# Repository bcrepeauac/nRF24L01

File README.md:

# nRF24L01
nRF24L01 adapter board for the SumoShield

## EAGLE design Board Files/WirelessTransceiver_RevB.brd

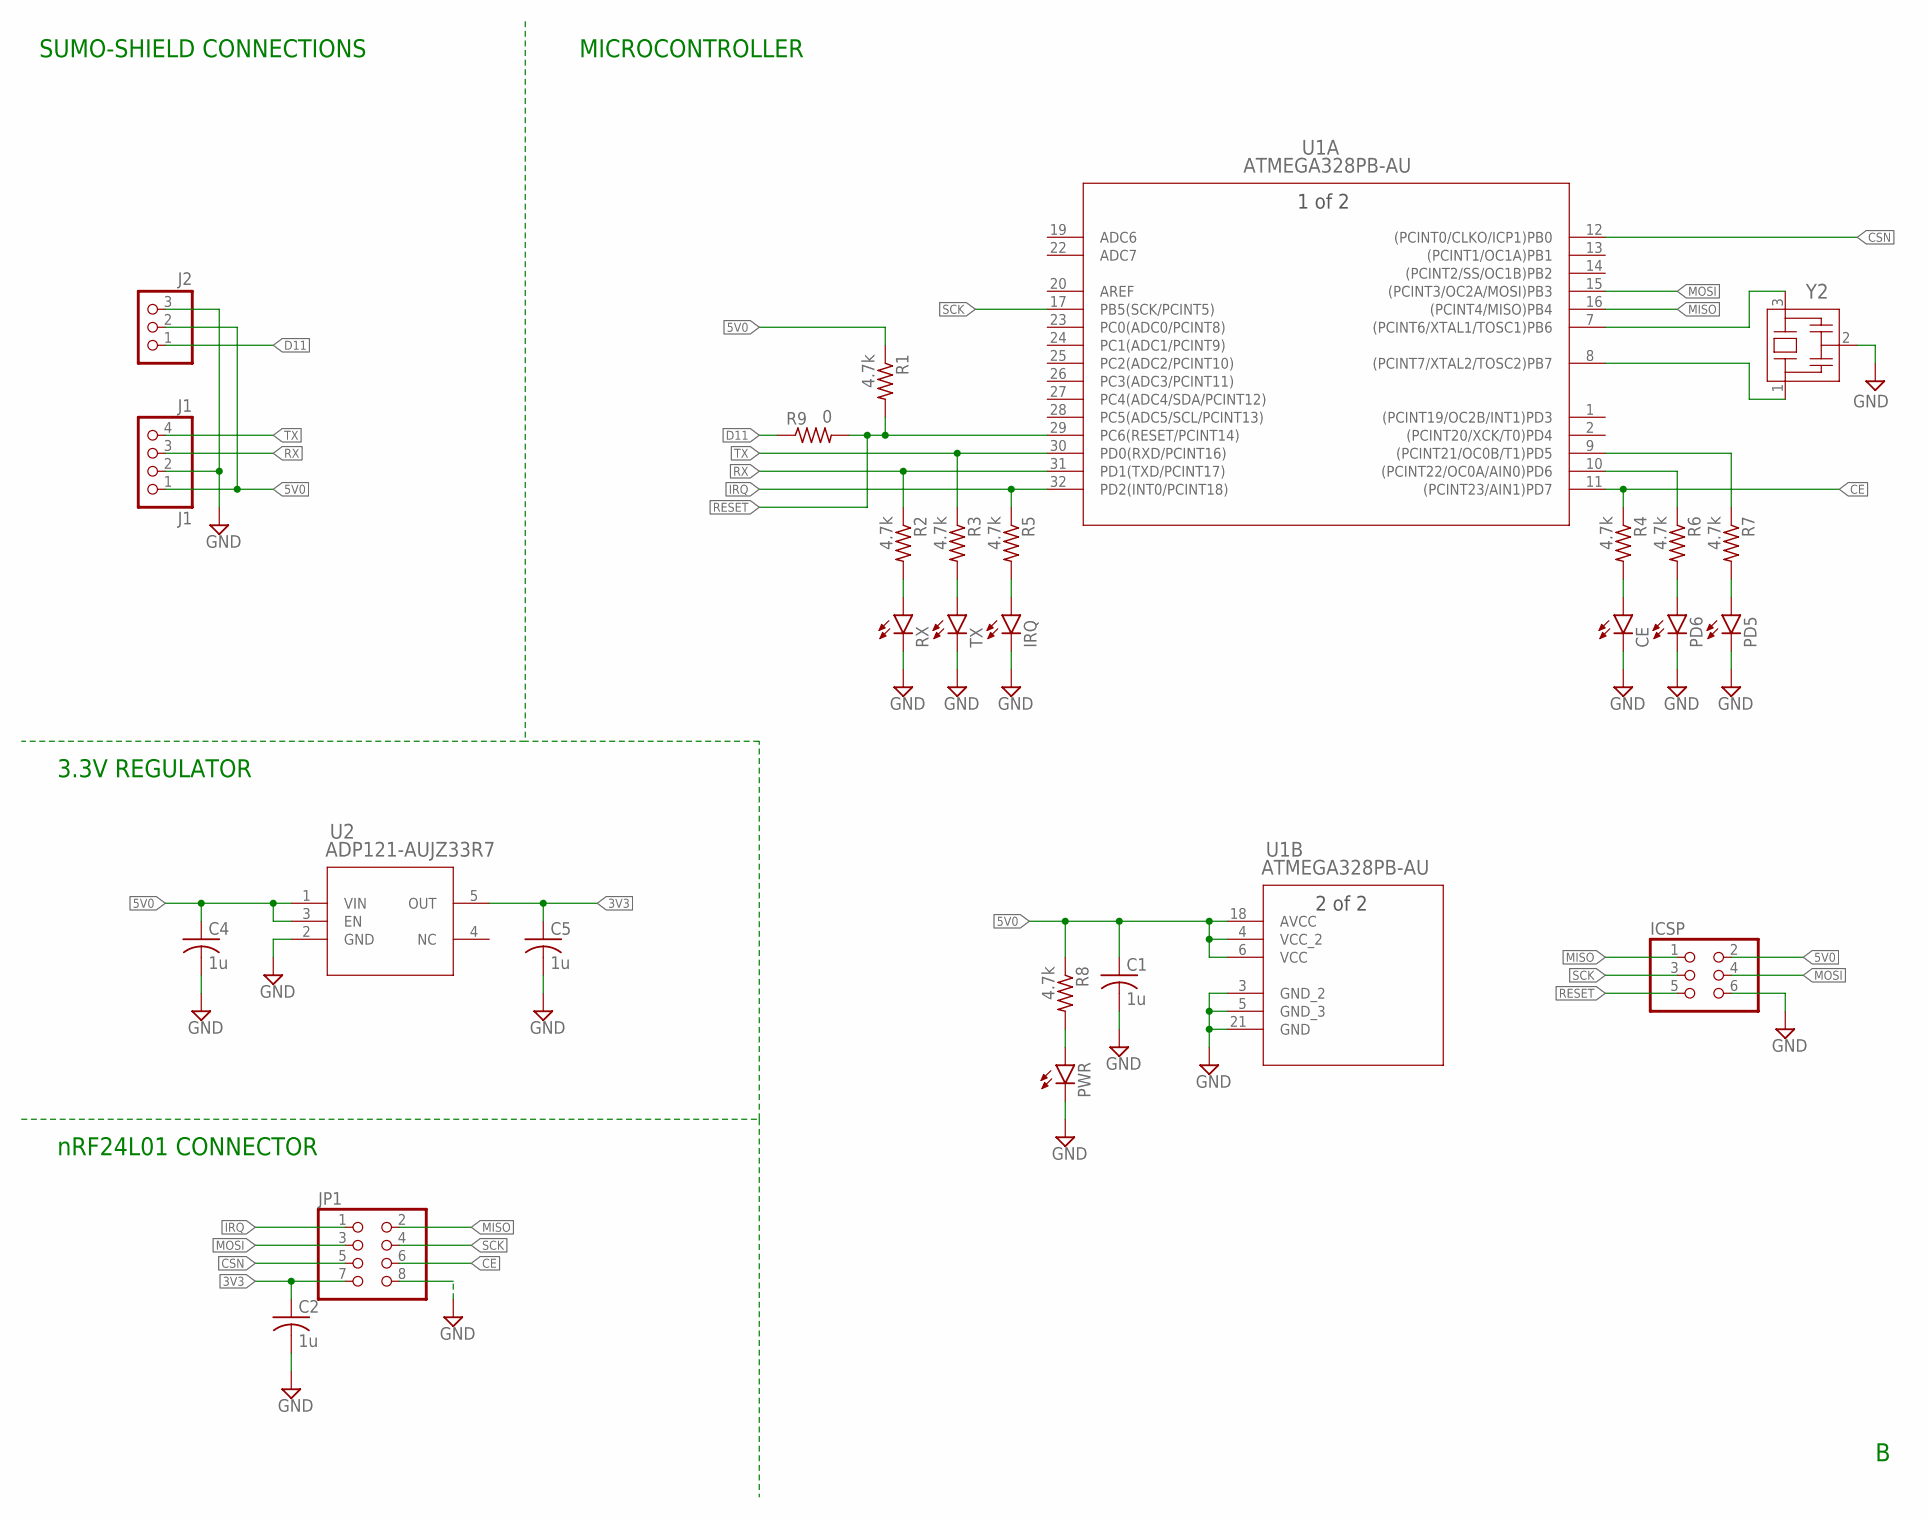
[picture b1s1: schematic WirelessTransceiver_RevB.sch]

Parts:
C1, C2, C4, C5: 1u; C0805
CE: LEDSML0805; SML0805
ICSP: PINHD-2X3; 2X03
IRQ: LEDSML0805; SML0805
J1: J1; 1X04
J2: PINHD-1X3; 1X03
JP1: PINHD-2X4; 2X04
PD5, PD6: LEDSML0805; SML0805
PWR: LEDSML0805; SML0805
R1, R2, R3, R4, R5, R6, R7, R8: 4.7k; R0805
R9: 0; R0805
RX: LEDSML0805; SML0805
TX: LEDSML0805; SML0805
U1: ATMEGA328PB-AU; 32A_MCH
U2: ADP121-AUJZ33R7; UJ_5_ADI
Y2: CSTNE16M0V530000R0; CSTNE16M0V530000R0_MUR

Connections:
3V3: C2.1, C5.1, JP1.7, U2.5 (OUT)
5V0: C1.1, C4.1, ICSP.2, J1.1, J2.2, R1.1, R8.1, U1.4 (VCC_2), U1.6 (VCC), U1.18 (AVCC), U2.1 (VIN), U2.3 (EN)
CE: JP1.6, R4.1, U1.11 ((PCINT23/AIN1)PD7)
CSN: JP1.5, U1.12 ((PCINT0/CLKO/ICP1)PB0)
D11: J2.1, R9.1
GND: C1.2, C2.2, C4.2, C5.2, CE.C, ICSP.6, IRQ.C, J1.2, J2.3, JP1.8, PD5.C, PD6.C, PWR.C, RX.C, TX.C, U1.3 (GND_2), U1.5 (GND_3), U1.21 (GND), U2.2 (GND), Y2.2
IRQ: JP1.1, R5.1, U1.32 (PD2(INT0/PCINT18))
MISO: ICSP.1, JP1.2, U1.16 ((PCINT4/MISO)PB4)
MOSI: ICSP.4, JP1.3, U1.15 ((PCINT3/OC2A/MOSI)PB3)
unnamed: R2.2, RX.A
unnamed: U1.7 ((PCINT6/XTAL1/TOSC1)PB6), Y2.3
unnamed: U1.8 ((PCINT7/XTAL2/TOSC2)PB7), Y2.1
unnamed: R3.2, TX.A
unnamed: CE.A, R4.2
unnamed: IRQ.A, R5.2
unnamed: PD5.A, R7.2
unnamed: PD6.A, R6.2
unnamed: PWR.A, R8.2
PD5: R7.1, U1.9 ((PCINT21/OC0B/T1)PD5)
PD6: R6.1, U1.10 ((PCINT22/OC0A/AIN0)PD6)
RESET: ICSP.5, R1.2, R9.2, U1.29 (PC6(RESET/PCINT14))
RX: J1.3, R2.1, U1.31 (PD1(TXD/PCINT17))
SCK: ICSP.3, JP1.4, U1.17 (PB5(SCK/PCINT5))
TX: J1.4, R3.1, U1.30 (PD0(RXD/PCINT16))

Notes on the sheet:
SUMO-SHIELD CONNECTIONS
3.3V REGULATOR
nRF24L01 CONNECTOR
MICROCONTROLLER

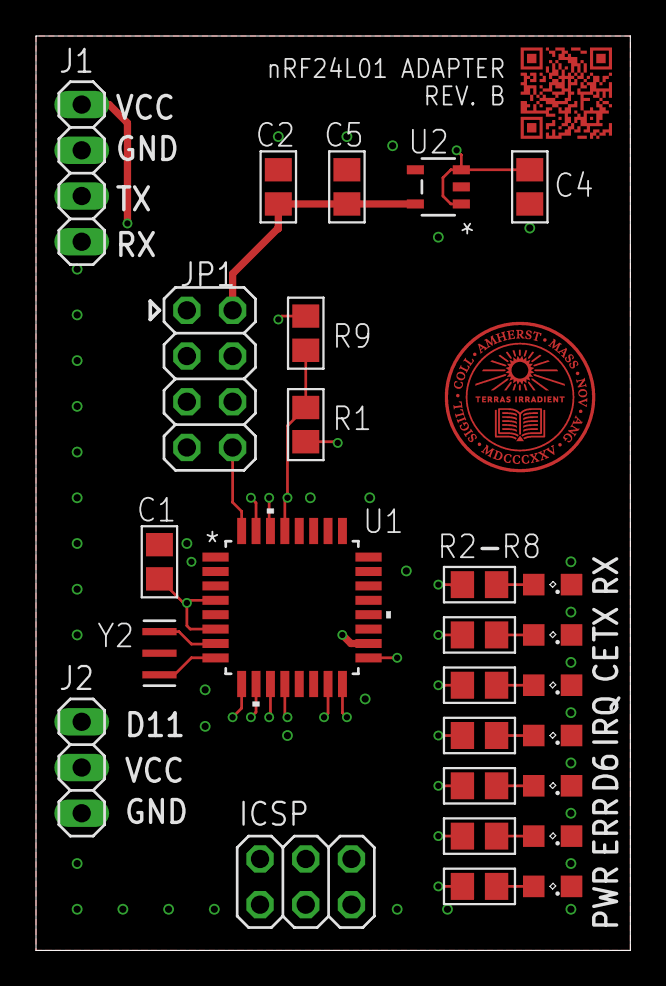
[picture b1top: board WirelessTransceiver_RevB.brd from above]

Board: 4 copper layers, 33.0 x 50.8 mm, 27 parts (0 on the bottom side), 24 nets.

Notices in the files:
parts and their libraries:
COPYRIGHT: Copyright (C) 2023 Ultra Librarian. All rights reserved.
